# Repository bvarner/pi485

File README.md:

# Pi485 - UART TTL (Raspberry Pi / Arduino) to RS485
## What is it?
Pi485 lets you connect the RX / TX pins on your Raspberry Pi (/dev/ttyAMA0) or Arduino device to an RS-485 network, 
and transmit / receive as if the network were a normal serial device.

## What can it do?
* Create a low-cost RS-485 network of devices using serial I/O.
* Communicate with other RS-485 networks.

Recent models of HVAC equipment (so called, "communicating" units) typically use RS-485 for the physical connection.
This makes deciphering the comms stream a software problem, and one that many people have already started working on!

## Features
All of the project variations in this repository feature the following:

* Termination Jumper. None of the commercial offerings or existing modules I've seen allow you to disable the termination resistor. On a 
multi-module RS-485 network, it's necessary that middle-nodes not have the termination resistor in the circuit, or the bus signals will 
deteriorate significantly.
* Hardware Latched DE / RE pins on the MAX485 driven by TX activity, with a 'RO' (Read Only) jumper header.
Adding a jumper will force your device to be 'read only' by disabling the hardware latch of the DE / RE Pins.
* Software controlable off / on. Using a GPIO pin (3.3v) you can turn the circuit 'on' or 'off', allowing for a software reset of the 485 
module, pseudo "power management", or simply give you the time to setup your UART tty before initiating a communication connection.
If you prefer the 'always on' approach, you can simply hook up positive voltage to the control pin, and the circuit will always be on.

## What's in this repository?
This repository contains [KiCad EDA](http://kicad.org/) source schematics, PCB layouts, and rendered SVG plots.

The SVG Plots can be used to print your own PCB, or you could try using them as a template for making your own.

## What? Make my own PCB?
I've had good success with the layouts in this repo using the laser-printer hot-iron transfer method. I've gotten excellent results with 
Hammermill Color Laser Gloss (sku 163110) paper. It's a 32lb very smooth gloss paper like you'll find on lightweight magazine covers.
The 163110 takes and transfers toner very well, and is light enough for use in nearly every laser printer I've run across.
When soaked in water for a few minutes after ironing the paper easily peels off without removing the toner. I normally lightly sand the 
left-over transfer with 1500 grit paper to remove the last of the paper fibers and any gloss 'bleed' before chemical etching the board.

Now that I have my method down I could probably tweak the layouts to shrink the trace size (from 1.0 to 0.8 or 0.7) which would help with
some of the 'bleed' I sometimes get when doing the iron transfer.

I also have invested in some inexpensive carbide drill bit sets from 0.3 - 1.2mm for drilling the PCBs in a drill press.

If you're interested in a prebuilt board, contact me (bvarner) via github. I would be willing to coordinate a small run, and I may have a 
few boards on hand (or on ebay) you could convince me to part with.

## Usage
To setup a RaspberryPi so that you can use the UART for what you want rather than it exposing a serial console.

1. Use `raspi-config` to disable the serial console.
2. Enable the UART at boot by editing `/boot/config.txt` and setting `enable_uart=1`.
3. A pi485 requires a logic 'high' signal on the PWR (P1 connector, pin 5) signal line. You can wire up a +3.3v line to force power to always
be 'on', or you can control it with a GPIO pin.

If using a GPIO pin, a convenient way to manage this is to install `wiringpi`, and edit the `/etc/rc.local` script to add the following lines:
```
/usr/bin/gpio mode 1 out
/usr/bin/gpio write 1 1
```

You can also take the opportunity to set your tty settings in `/etc/rc.local` if you so desire.

## Hardware Configurations

### Standalone
This complete solution can be assembled from discrete components. It uses a Max485 IC, and NE555 timer, and some discrete components to 
implement a hardware level RS-485 interface that automatically controls the DE / RE pins based on TX activity, allows for jumper 
configuration of termination, and adds blinken-lights for TX / RX, and Power.

This configuration is the easiest one to fabricate at home. Everything from pad size, to trace width and clearance restrictions have been
tweaked to make this easier to work with for novices. Armed with a single-sided copper clad board, some ferric chloride, a fine-tipped 
sharpie marker and a steady hand, you could build this layout without doing an iron transfer. However, the component cost is higher. The
PDIP Max485 in small quantities is by itself more expensive than a single LC Technologies RS485 module used by the bearer configuration.

### Bearer
The bearer board is designed to hold an [LC Tech MAX485 module](http://www.chinalctech.com/index.php?_m=mod_product&_a=view&p_id=811), which
is an inexpensive module based around a max485 in a surface-mount, slew-rate limited configuration. 
These modules include some support components like power filtering capacitors, a power LED, and some pull-up resistors.
Building a bearer board is a bit more tricky, as it has lower clearance tolerances between traces, thinner traces, and requires that you 
modify (unsolder) some resistors off the LC Tech module. However, when full BOM part costs are taken into consideration, if you're making
more than one pi485, it'll be cheaper to use the bearer configuration.

The bearer board adds the 555 latch circuit for DE/RE control from the TX line, RX / TX LEDS, power on/off, and 
jumper termination control from the standalone board design (if you unsolder the 120Ohm resistor on the LC Tech module).

In my experience, if you want to make more than one of these devices, it's much cheaper to purchase the LC Tech modules and build Pi485 
bearer boards to hold them.

## Project Background
I've had a couple Raspberry Pi's laying about my home for a few years now. After running across the 
[Infinitude project](https://github.com/nebulous/infinitude), I realized that my 
HVAC system (a Bryant unit) is actually a 'communicating' system as well. I've had in the back of my mind for some time a project to hook up
a raspberry pi, and track long-term time-series data on my HVAC unit, performance, and temperature differentials.

### Off The Shelf Module Shortcomings / Circuit Analysis / Reasons this project exists.

Almost every module I've looked at is based on the [MAX485](http://datasheets.maximintegrated.com/en/ds/MAX1487-MAX491.pdf).

#### Overly simplistic opinionated view of RS-485.
It seems that off-the-shelf modules tend to approach the MAX485 series of half-duplex (two wire RS485) chips as a pretty simple TTL->485 
converter, suitable for locating at the _endpoints_ of a very simplistic single master-slave network. In order to drop in multiple modules 
(multiple slaves) or enable multi-master communications and form a true network, there's some hardware work that needs to be done (removing
termination resistors) and software control of the RE / DE with a GPIO (which open you up to a whole slew of software timing issues).

#### Soldered on Termination
For example, the LinkSprite module and the LC Tech modules both carry 120Ohm termination resistors, and no jumper header to remove it from
the circuit. The only practical option to add these modules as a network node other than an 'end point' is to unsolder that resistor.

#### Lack of TX / RX Visibility
I like [blinkenlights](https://en.wikipedia.org/wiki/Blinkenlights). These products should have blinkenlights.

#### DE / RE Pin Hysteresis 
Additionally, the LC Tech module has the DE and RE pins of the Max485 directly accessible over headers but provides no extra circuitry to 
drive the input to those pins based off the TTL TX. These two pins of a Max485 are responsible for setting the duplex state of the chip 
(Driver Enable / Receiver Enable) for either sending or receiving data. The RE pin is active on Logic Low (GND) and the DE pin is active on 
Logic High (~20ma of forward voltage). For this reason, you'll commonly see these pins wired together. When set High, the Max485 disables
receiving, and enables transmitting. When pulled low, it enables receiving and disables transmitting. The LC Tech module seems to defy all 
logic and reason in how it wires up the DI, DE, RE, and RO pins. Each pin has a 10k pull-up resistor. So unless you're actively draining 
these pins to ground with your logic circuits,  your max485 is going to end up in "write" mode by _default_. In a multi-master half-duplex
system like an HVAC unit (the initial target application for pi485) this causes a big problem.

I've found many schematics which suggest tying the DE / RE pins to a separate GPIO. This is a terrible idea in practice. In a busy RS485 bus
the time between the DI/DE pins shifting and the start of output on the TX pin would effectively guarantee a collision on the network.

I've also found schematics for RS-232 -> RS-485 converters which work by converting the 232 signal to TTL, then the TTL to RS-485. In these
circuits, they tend to leverage a 555 timer as a time-delayed latch, to hold the DE / RE pins in transmit mode based on the state of the TTL
TX pin. This seems like a really good idea in theory, and in circuit simulations (I don't have a physical scope) it appears that the 555
output will respond quickly enough for at least a 38400baud network to cleanly communicate all the necessary symbols over the wire (given 
the sizing of resistors and capacitors in use with the 555).

In this [555 TTL Latch Simulation](http://tinyurl.com/hx6gfwh), there's a +5V supply, GND, and a H/L logic input (clickable) on the left. 
The output pin of the 555 has a H/L output detector on it, and drives an NPN transistor to turn on an LED. In a real circuit using this 
technique, the 555 output pin would drive the DE/RE pins on a Max485. As an example, checkout the 
[AVT530](http://serwis.avt.pl/manuals/AVT530.pdf), an RS232 to RS485 converter that uses TTL as an intermediary. The schematic is on page 2.

The same company also uses this same 555 & Max485 circuit on their [USB to RS485](http://serwis.avt.pl/manuals/AVT530USB.pdf) converter.

The down-side with these circuits, is that there is a timing differential after the TX pin stops transmitting that the RE pin is held high.
Recall earlier I mentioned things about start / stop bits? This is where that comes into play.
At 38400Hz (as in the simulation above) this delay accounts for an entire clock cycle of bit transmission on the bus. In the interactive 
simulations above, note how if you switch the TTL input high (0 or idle) it takes 2 clocks before the 555 sets the output back low. If your
bit protocol doesn't include a stop bit (idle / high) then the DE / RE will not be disabled at the appropriate time. Without stop bits, you 
will transmit one extra idle (logical 1) on the 485 bus and miss receiving a bit for a clock with these latched circuits.

Here's another [simulation of the 555 latch circuit with pulsed input](http://tinyurl.com/hn6zreu). In this revision, we've added a pull-up
resistor (5k) to the input trigger to hold it 'high' when idle, moved the input clk to drive a decade counter, and tied output pins from the
counter to switch an NPN transistor that sinks the trigger pin low when the counter has a high output. Think of the counter as sending 
logical 1's and 0's by pushing a switch. When the switch (transistor) is closed, the TR voltage drops to ground. If you have start or stop
bits enabled in your stream, this initial drop (0) will be the start bit, which will trigger the 555 output high. In the AVT circuits, this 
drives the RE / DE pins high, putting the MAX485 into transmit mode. An idle 'high' stop bit (Q8) will let the timer's capacitor drain, 
resetting it's output pin. But if you're not using start / stop bits... and you're just getting a stream of bits that is synchronized 
in software, then using a 555 latch is going to be asking for trouble.

In looking at the LinkSprite module, I found it interesting that it dispenses with a time-delay latch and supplies power to the DE / RE pins
via MOSFETS switching a 0.33mA current based upon the TX input. This seems rather 'icky' to me, since logically I would think the DE / RE
pins going 'high' whenever the TTL signal goes idle, would cause an issue. So I threw together a 
[simulation of the TTL input with MOSFET](http://tinyurl.com/glnvxa2) triggers. This confirmed what I thought as far as behavior without 
delay. The good news here, is if you're sending a '0' on the RS-485 bus, you'll transmit that 0, and be prepared to receive any values from
the bus immediately afterward. So if your protocol doesn't use stop bits, you'll be able to read the stream without error. The natural
question at this point is, "what if I'm trying to transmit a '1' (logical TTL high / idle value)?" In that case, the DE pin would be pulled
low, along with the RE pin, putting the MAX485 into Driver disable, Receiver Enabled mode. I'm not sure if this would effectively pulse the
RS-485 bus in an appropriate manner. The Bus signals bits based on bias differences between the two wires, A and B. Something about this
arrangement smells funny.

According to the stuff I've read on RS-485, a driver 'idle' would be A+, B- potentials. After pouring over the Max485 datasheet, I don't see
anything that will lead me to believe RE high / DE low would result in A+, B- potentials being emitted on output lines of the chip.

Nevertheless, it must work... right? Unless the LinkSprite and LC Tech components aren't being tested in multi-master half-duplex 
networks. I have a feeling that's exactly what's going on, since they both carry soldered-on termination resistors that cannot be 
jumper-disabled. That means that if you introduced a network of these devices with more than two nodes, you'd have pretty significant signal
degradation.

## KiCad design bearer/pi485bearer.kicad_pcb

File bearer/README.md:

# Pi485 Bearer Module

Based upon what I learned while creating the Standalone pi485, this board is meant to function as a carrier / bearer for an
[LC Technologies RS485 module](http://www.chinalctech.com/index.php?_m=mod_product&_a=view&p_id=811), adding the RX / TX LEDs,
power controll, and latched DE / RE pin driving to this very inexpensive and commonly available module.

Unlike the standalone board this layout prioritizes compactness over ease of use for beginners.
The trace clearances are tighter and you'll need to remove five surface mount resistors from the RS485 module. In practice, I've found 
these boards are reasonably easy to produce with a laser printer hot iron transfer.

## PCB Layout

is designed to hold these RS485 modules

## Schematic

# Design Goals
* Add the functions and features of the standalone module in a slightly more compact layout that can accomodate inexpensive 485 modules.
* Leverage the RS 485 module due to the module cost being less than the the cost of a discrete terminal block header, max485 IC, power LED, 
LED resistor, and filtering capacitors. These boards do shave a couple USD off the cost of UART based RS-485.
* Latch the DE / RE pins on the Max485 based upon the UART TX activity, but allow that to be disabled (force read-only mode)
* Include jumper termination for the A/B lines of the RS485 bus.

For in-depth details on the function of [the circuit](plots/pi485bearer.png) refer to the [Standalone Module README](../standalone/README.md).

# Build Instructions

1. Start off by customizing the resistor values for your LEDs. I used [http://ledcalc.com/] to help inspire my choices.
2. Use KiCad's PCB editor (pcbnew) to customize any footprint changes.
3. Print the [back copper](plots/pi485bearer-B.Cu.svg) layer on a laser printer, using glossy photo paper.
4. Print the [front](plots/pi485bearer-brd.svg) layers on a laser printer, using glossy photo paper.
5. Cut your board (62mm x 30mm)
6. Transfer the copper printout using a hot iron and some water.... (youtube reference coming). Touchup with a resist pen if necessary.
7. Etch the board.
8. Clean the board.
9. Tin the board.
10. Reflow the board (bake it in an oven).
11. Drill the component holes.
12. Place & solder components.
13. Assemble!
14. Remove the 120Ohm resistor (R7), and the 4 10kOhm pull-up resistors (R1 - R4) from the LC Tech 485 Module.

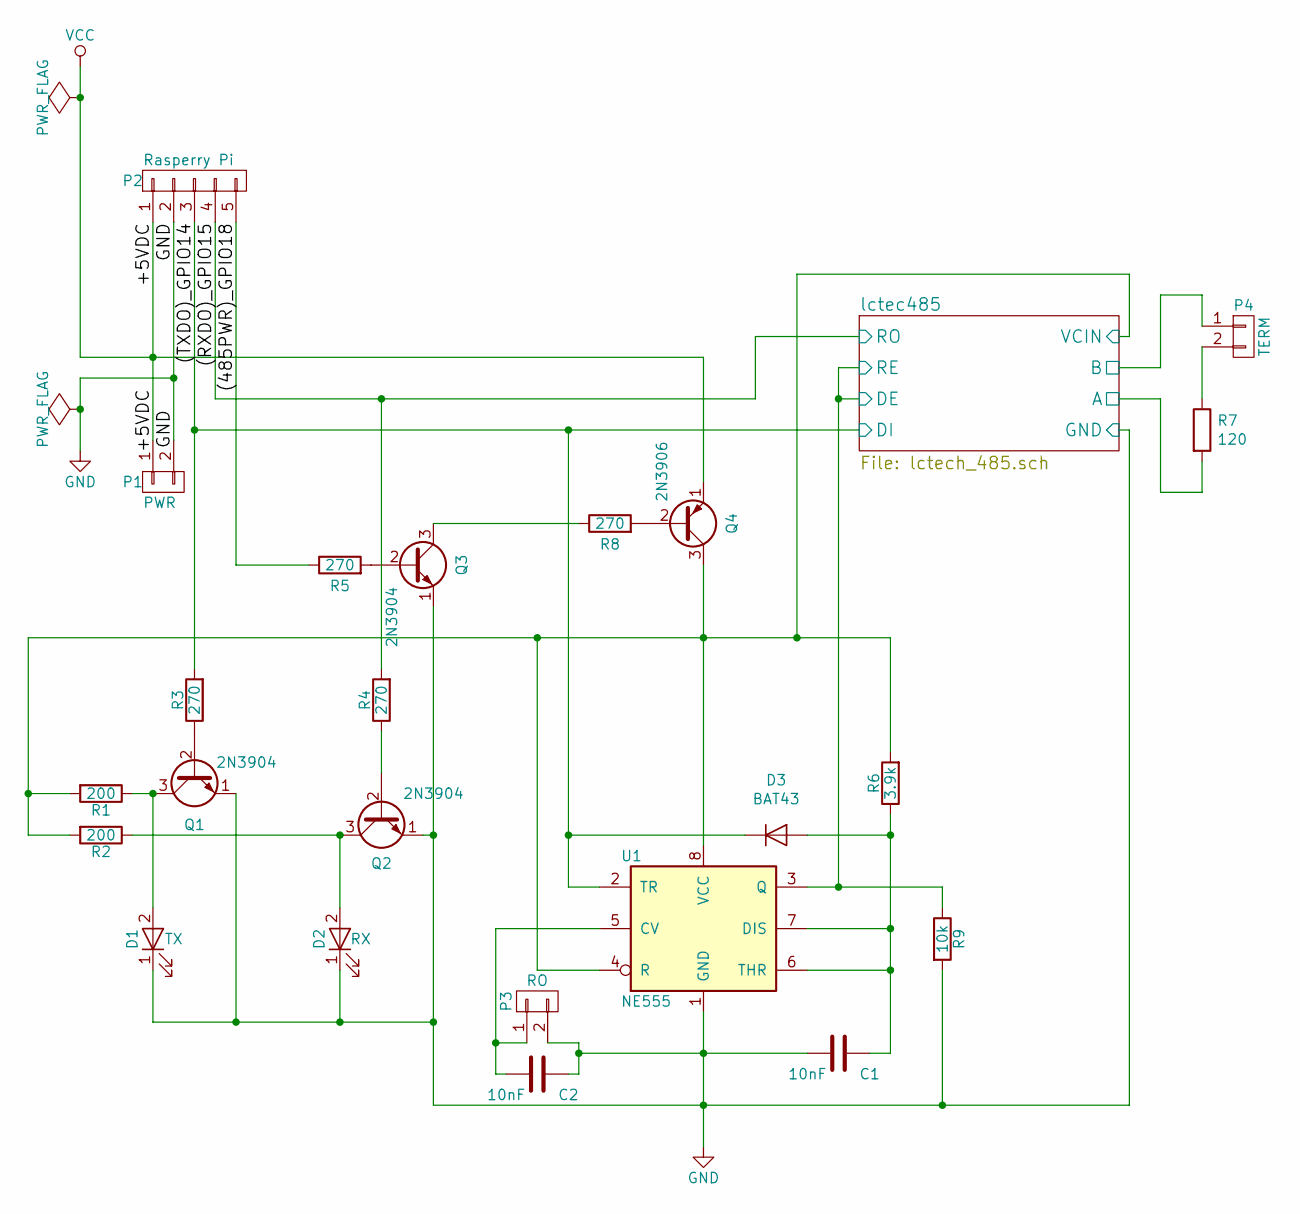
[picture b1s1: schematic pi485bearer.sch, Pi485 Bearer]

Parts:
C1, C2: 10nF; C_Rect_L4_W2.5_P2.5
D1: TX; LED-3MM
D2: RX; LED-3MM
D3: BAT43; Diode_DO-35_SOD27_Horizontal_RM10
P1: PWR; Pin_Header_Straight_1x02
P2: Rasperry Pi; Pin_Header_Straight_1x05
P3: RO; Pin_Header_Straight_1x02
P4: TERM; Pin_Header_Straight_1x02
Q1, Q2, Q3: 2N3904; TO-92_Inline_Wide
Q4: 2N3906; TO-92_Inline_Wide
R1, R2: 200; Resistor_Horizontal_RM7mm
R3: 270; Resistor_Horizontal_RM10mm
R4, R5, R8: 270; Resistor_Horizontal_RM7mm
R6: 3.9k; Resistor_Horizontal_RM10mm
R7: 120; Resistor_Horizontal_RM10mm
R9: 10k; Resistor_Horizontal_RM15mm
U1: NE555; DIP-8_W7.62mm_LongPads

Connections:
/(485PWR)_GPIO18: P2.5, R5.1
/(RXDO)_GPIO15: P2.4, R4.2; also elsewhere on the board
/(TXDO)_GPIO14: D3.1 (K), P2.3, R3.2, U1.2 (TR); also elsewhere on the board
/lctec485/A: R7.2; also elsewhere on the board
/lctec485/B: P4.1; also elsewhere on the board
/lctec485/DE: R9.1, U1.3 (Q); also elsewhere on the board
/lctec485/VCIN: Q4.3 (C), R1.2, R2.2, R6.2, U1.4 (R), U1.8 (VCC); also elsewhere on the board
GND: C1.2, C2.1, D1.1 (K), D2.1 (K), P1.2, P2.2, P3.2, Q1.1 (E), Q2.1 (E), Q3.1 (E), R9.2, U1.1 (GND); also elsewhere on the board
unnamed: C1.1, D3.2 (A), R6.1, U1.6 (THR), U1.7 (DIS)
unnamed: C2.2, P3.1, U1.5 (CV)
unnamed: D1.2 (A), Q1.3 (C), R1.1
unnamed: D2.2 (A), Q2.3 (C), R2.1
unnamed: P4.2, R7.1
unnamed: Q1.2 (B), R3.1
unnamed: Q2.2 (B), R4.1
unnamed: Q3.2 (B), R5.2
unnamed: Q3.3 (C), R8.1
unnamed: Q4.2 (B), R8.2
VCC: P1.1, P2.1, Q4.1 (E)

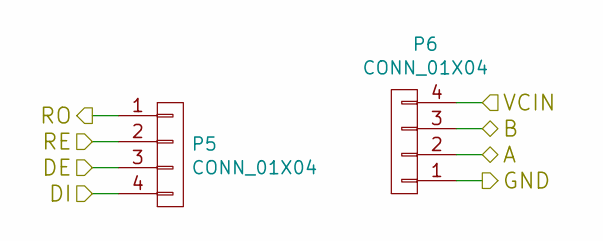
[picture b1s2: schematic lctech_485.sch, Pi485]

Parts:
P5, P6: CONN_01X04; Socket_Strip_Straight_1x04

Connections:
/(RXDO)_GPIO15: P5.1; also elsewhere on the board
/(TXDO)_GPIO14: P5.4; also elsewhere on the board
/lctec485/A: P6.2; also elsewhere on the board
/lctec485/B: P6.3; also elsewhere on the board
/lctec485/DE: P5.2, P5.3; also elsewhere on the board
/lctec485/VCIN: P6.4; also elsewhere on the board
GND: P6.1; also elsewhere on the board

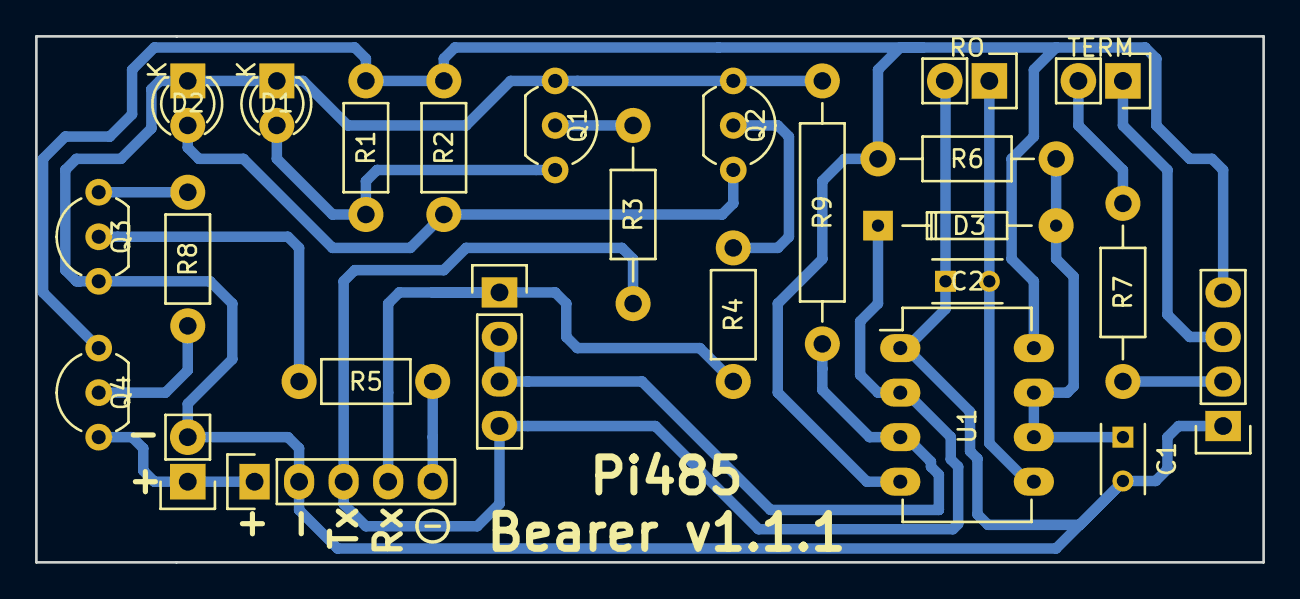
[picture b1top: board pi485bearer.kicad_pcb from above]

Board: 2 copper layers, 70.0 x 30.0 mm, 25 parts (0 on the bottom side), 19 nets.

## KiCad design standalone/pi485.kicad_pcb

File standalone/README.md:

# Pi485 Standalone Module

This is a stand-alone module for RS-485 communication, utilizing a MAX485 IC and a NE555 Timer IC.
The PCB for this project is the most 'simple' of the two to etch yourself. Most of the pads are 
oversized, the copper traces are significantly wider and spaced far enough that it's possible 
to create a PCB with a resist marker by hand. 

## PCB Layout

## Assembled

## Schematic

# Design Goals
* [Simple / Easy To Understand Circuit](plots/pi485.png)
* Easily fabricated at home with simple tooling
* Reasonably inexpensive to source parts for and build (~$20 or less)
* Latch the DE / RE pins on the Max485 based upon the UART TX activity, but allow that to be disabled (force read-only mode)
* Include jumper termination for the A/B lines of the RS485 bus.

To achieve these goals the PCB layout in this repository is a single-side clad board, components on the front, copper on the back.
The traces are large (0.4mm!), the pads are oversized where possible, and I've allowed plenty of clearance between traces and pads, making
it possible to touch-up a hot-iron transfer with an ink-resist pen. You may even be able to draw the existing tracks with a pen free-hand.

For tooling, you'll need the 'standard' PCB etching supplies; a bottle of Ferric Chloride, some isopropyl alcohol, gloves, 
a dish to do the etching, and an appropriately sized drill bit. (I had a 0.040" bit in a set) I'd recommend you have a drill press, too.

I highly recommend doing a hot-iron transfer of laser printer toner. Print the SVGs using a laser printer onto glossy photo (or magazine)
paper. Heat the board with an iron, then stick the printout to the board. Press the printout firmly to the board using the hot iron (you're
goal is to melt the toner to the board surface), and then start soaking with water and continue steaming. Firm pressure and heat will do a
good job of sticking the printout onto the board. It works surprisingly well. Once you've steamed the paper (or soaked it in water) and it
starts to fall of the board, you can touchup any trace or pad issues with a resist pen, and etch the board.

I also use a kitchen oven to bake the board once it's tinned. Getting it up to ~425 degrees F does a nice job of reflowing the solder,
which makes it much easier to drill the holes.

# Circuit Analysis / Explanation

## TTL Serial Communication Basics
TTL signaling of serial data idles 'high'. When data is being transmitted on the TX pin, it first drops 'low' (a start bit), 
transmits it's data, and then sends a stop bit. In TTL, a logical 0 is GND. A Logical 1 is +V. But when there are no transmissions taking 
place, the pin holds 'high', at +V. I personally found [this SparkFun tutorial](https://www.sparkfun.com/tutorials/215) to be highly 
educational on the nuances of TTL. If your protocol doesn't include a start / stop bit, this can be problematic for converting TTL 
_transmissions_ to RS-485.

## Schematic Breakdown
The [current schematic](plots/pi485.png) is fairly straightforward.

All of the resistor values connected directly to LEDs should be double-checked for your LED selections.

## Power Input / Signal Connections
Starting in the upper left quadrant of the schematic, you have the input header pins (P1). There's a second pair of headers for an additional
+5vdc and ground connections (P2). I use the second two-pin header to connect my power supply, then connect the other pins to the Pi providing
power to the RaspberryPi and connecting the UART pins and 485PWR signal line.

## RX / TX LED Signaling
The RX & TX lines are tapped with 270ohm resistors to pull the 5vdc down to an appropriate level for tripping the NPN transistors in the 
lower left side of the schematic. When the voltage on the RX / TX pins goes LOW (signaling data, not idle), the NPN halts the flow of 
electricity from the Collector to the Emitter (opens the switch), leaving the only path to ground being through the LEDs. Make sure you 
size your R3 and R7 resistors appropriately for your LEDs. The NPN transistors in this circuit are specced as 2N3904's, but 2N4401s will 
work just as well.

## Power Filtering & Power LED 
Above the RX / TX LED section, there's a small block with two transistors (an NPN and a PNP) working together to create a 'high-side' power
switch for the entire circuit. The PNP transistor switches the +5v supply for the rest of the circuit, based on the on/off state of the 
NPN. Using the NPN to control the PNP allows us to drive the 5v line with a 3.3v GPIO, and to do it in a '1' is on, '0' is off, semantic.

If you'd rather the circuit always be 'on', omit these components, or connect pin 5 on the P1 header to the 5V or a 3.3V line.

Looking to the lower-right portion of the schematic, you'll find several decoupling filter capacitors and a power LED.

## UART TX Connections
The TX line is connected to the trigger pin of a 555 timer, and then to the Data Input pin of the Max485.

The 555 timer circuit is a slightly modified missing pulse detector, which you'll find right smack in the middle of the schematic.

When the TX power drops below the threshold defined by the 3.9k resistor (R2), the output of the 555 goes HIGH. After a very short delay,
(it switches ~38400hz) the output will go back low, unless the the TX line input is still low. In a typical missing pulse detector, the 555
output will go back low regardless of the TX line (555 trigger) input. The addition of the shottky diode changes this configuration, and 
holds the output steady so long as the input is steady. The diode has to be capable of switching reverse voltage bias fast enough to keep
the input lower than the threshold / discharge output, but without affecting the input signal line. Hence the use of the BAT43, rather than
a 'normal' silicon diode.

The output of the 555 timer is used to set the input on the DE / RE (Driver Enable / Receiver Enable) pins on the max485. When HIGH, the 
Driver Enable is set, putting the Max485 into 'master' mode and broadcasting on the 485 bus. When LOW, the RE pin (which has inverted logic
on a Max485) is enabled, putting the Max485 into 'receive' mode.

If there is a jumper present on the CTRL pin (5) of the 555 timer, the 555 output will always be 'LOW' effectively holding the Max485 in 
Receive mode forever.

## UART RX Connection
Moving along the RX line, it's connected to the Data Output pin of the Max485.

## Max485 Output
The output pins of the Max485 are configured to setup a high-resistance reference against the current 'ground', and to allow the termination
(120 Ohm) resistor to be removed from the circuit.

## Putting it all together...
The circuit provides basic decoupling / power filtering, some passive LED monitoring of RX / TX lines, and a latch-based DE / RE driver 
logic for the Max485, along with a basic resistance network to setup the A/B differentials on the RS-485 bus.

# Analysis of other products / options
I am not a professional EE. In reality I'm a software engineer who got into this out of curiosity. I have always detested 
black-boxes (things which I cannot take apart or understand completely) and it's my nature to dismantle, analyze, evaluate, and eventually 
take that knowlege and apply it to things I synthesize. I consider electronics a 'hobby'. My comments here are my own personal opinions
and are not an endorsement or meant to dissuade or persuade your purchasing decisions.

# Build Instructions

1. Start off by customizing the resistor values for your LEDs. I used [http://ledcalc.com/] to help inspire my choices.
2. Use KiCad's PCB editor (pcbnew) to customize any footprint changes.
3. Print the [back copper](plots/pi485-B.Cu.svg) layer on a laser printer, using glossy paper.
4. Print the [front](plots/pi485-brd.svg) layers on a laser printer, using glossy paper.
5. Cut your board to size (63mm x 46mm)
6. Transfer the copper printout using a hot iron and some water.... (youtube reference coming). Touchup with a resist pen if necessary.
7. Etch the board.
8. Clean the board.
9. Tin the board.
10. Reflow the board (bake it in an oven).
11. Drill the component holes.
12. Place & solder components.
13. Clean up, and enjoy!

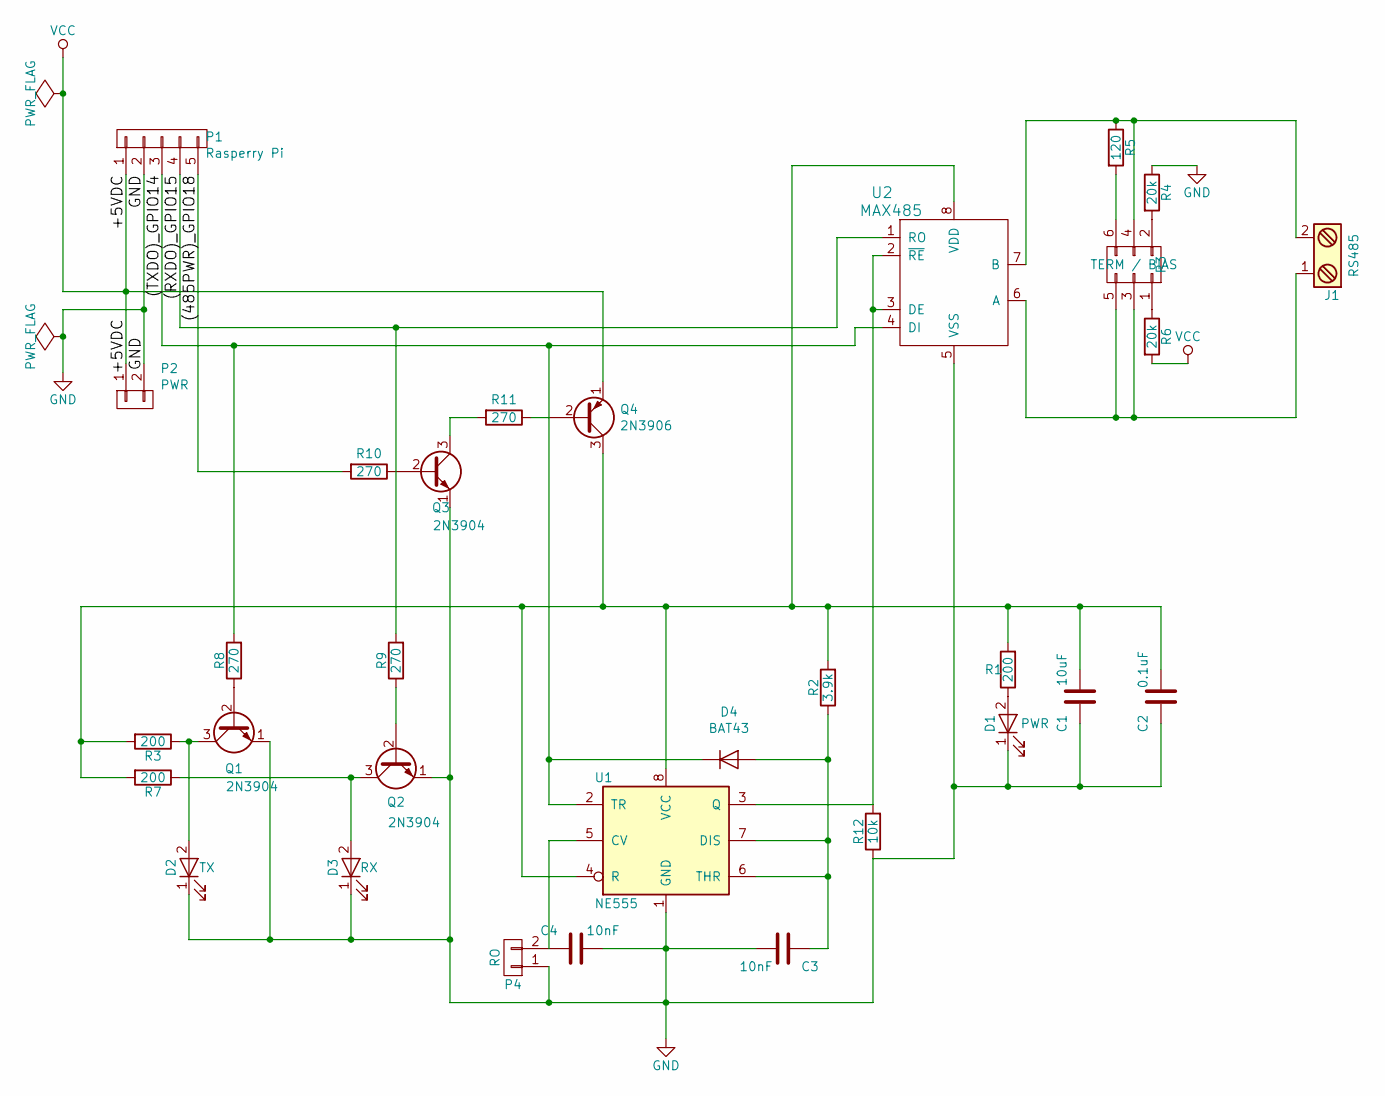
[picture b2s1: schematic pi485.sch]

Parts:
C1: 10uF; C_Radial_D5_L11_P2
C2: 0.1uF; C_Rect_L7_W2.5_P5
C3: 10nF; C_Rect_L7_W2.5_P5
C4: 10nF; C_Rect_L4_W2.5_P2.5
D1: PWR; LED-3MM
D2: TX; LED-3MM
D3: RX; LED-3MM
D4: BAT43; Diode_DO-35_SOD27_Horizontal_RM10
J1: RS485; TerminalBlock_Pheonix_MPT-2.54mm_2pol
P1: Rasperry Pi; Pin_Header_Straight_1x05
P2: PWR; Pin_Header_Straight_1x02
P3: TERM / BIAS; Pin_Header_Straight_2x03
P4: RO; Pin_Header_Straight_1x02
Q1, Q2, Q3: 2N3904; TO-92_Inline_Wide
Q4: 2N3906; TO-92_Inline_Wide
R1: 200; Resistor_Horizontal_RM7mm
R2: 3.9k; Resistor_Horizontal_RM10mm
R3, R7: 200; Resistor_Horizontal_RM10mm
R4, R6: 20k; Resistor_Horizontal_RM7mm
R5: 120; Resistor_Horizontal_RM10mm
R8, R9, R10, R11: 270; Resistor_Horizontal_RM10mm
R12: 10k; Resistor_Horizontal_RM7mm
U1: NE555; DIP-8_W7.62mm_LongPads
U2: MAX485; DIP-8_W7.62mm_LongPads

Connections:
/(485PWR)_GPIO18: P1.5, R10.2
/(RXDO)_GPIO15: P1.4, R9.2, U2.1 (RO)
/(TXDO)_GPIO14: D4.1 (K), P1.3, R8.2, U1.2 (TR), U2.4 (DI)
GND: C1.1, C2.1, C3.2, C4.2, D1.1 (K), D2.1 (K), D3.1 (K), P1.2, P2.2, P4.1, Q1.1 (E), Q2.1 (E), Q3.1 (E), R4.1, R12.1, U1.1 (GND), U2.5 (VSS)
unnamed: C1.2, C2.2, Q4.3 (C), R1.2, R2.2, R3.2, R7.2, U1.4 (R), U1.8 (VCC), U2.8 (VDD)
unnamed: C3.1, D4.2 (A), R2.1, U1.6 (THR), U1.7 (DIS)
unnamed: C4.1, P4.2, U1.5 (CV)
unnamed: D1.2 (A), R1.1
unnamed: D2.2 (A), Q1.3 (C), R3.1
unnamed: D3.2 (A), Q2.3 (C), R7.1
unnamed: J1.1, P3.3, P3.5, U2.6 (A)
unnamed: J1.2, P3.4, R5.1, U2.7 (B)
unnamed: P3.1, R6.1
unnamed: P3.2, R4.2
unnamed: P3.6, R5.2
unnamed: Q1.2 (B), R8.1
unnamed: Q2.2 (B), R9.1
unnamed: Q3.2 (B), R10.1
unnamed: Q3.3 (C), R11.2
unnamed: Q4.2 (B), R11.1
unnamed: R12.2, U1.3 (Q), U2.2 (~RE), U2.3 (DE)
VCC: P1.1, P2.1, Q4.1 (E), R6.2

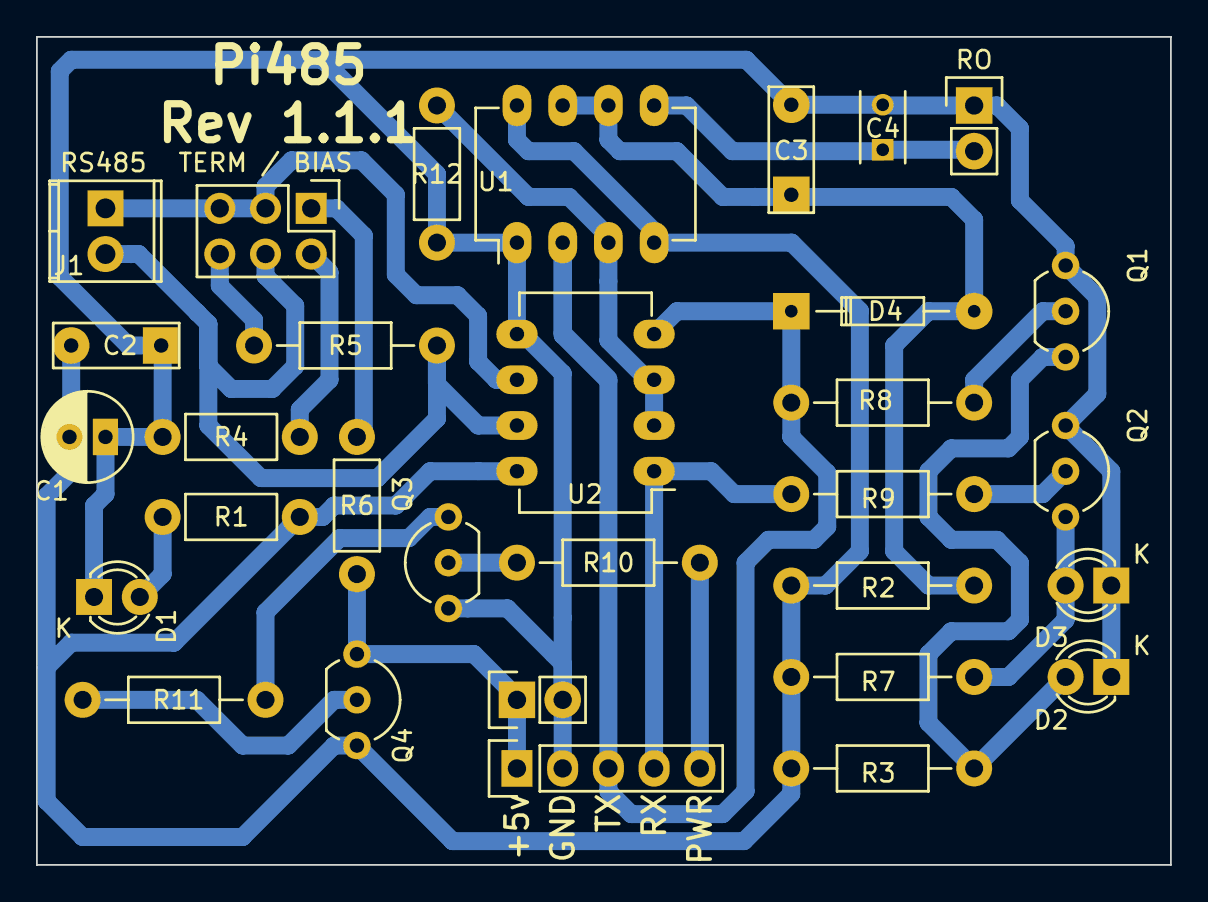
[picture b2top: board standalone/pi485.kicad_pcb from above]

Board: 2 copper layers, 63.0 x 46.0 mm, 31 parts (0 on the bottom side), 22 nets.

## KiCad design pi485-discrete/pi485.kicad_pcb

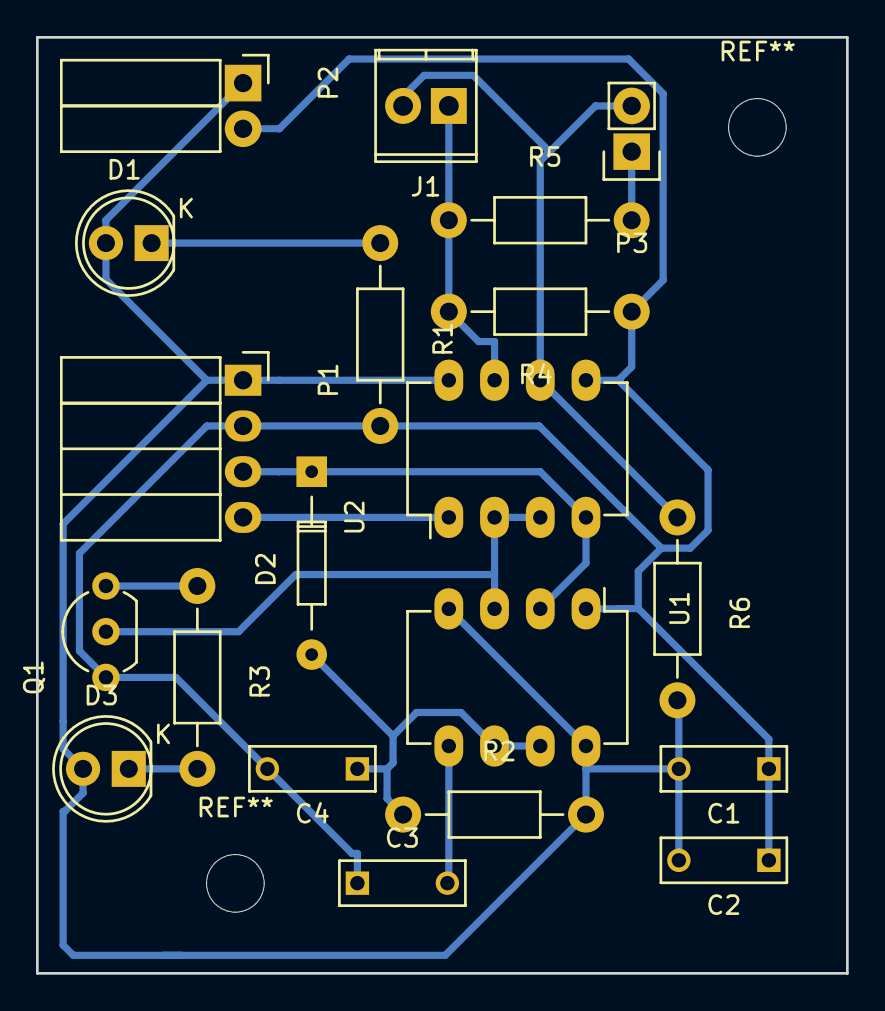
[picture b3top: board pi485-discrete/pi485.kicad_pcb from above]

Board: 2 copper layers, 45.0 x 52.0 mm, 20 parts (0 on the bottom side), 13 nets.

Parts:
C1: 0.1uF; C_Rect_L7_W2.5_P5
C2: 10uF; C_Rect_L7_W2.5_P5
C3, C4: 10nF; C_Rect_L7_W2.5_P5
D1: PWR; LED-5MM
D2: BAT43; Diode_DO-35_SOD27_Horizontal_RM10
D3: TX; LED-5MM
J1: RS485; TerminalBlock_Pheonix_MPT-2.54mm_2pol
P1: Rasperry Pi; Socket_Strip_Angled_1x04
P2: PWR; Socket_Strip_Angled_1x02
P3: Term; Pin_Header_Straight_1x02
Q1: NPN; TO-92_Inline_Wide
R1: 1k; Resistor_Horizontal_RM10mm
R2: 3.9k; Resistor_Horizontal_RM10mm
R3: 470; Resistor_Horizontal_RM10mm
R4, R6: 20k; Resistor_Horizontal_RM10mm
R5: 120; Resistor_Horizontal_RM10mm
U1: NE555; DIP-8_W7.62mm_LongPads
U2: MAX485; DIP-8_W7.62mm_LongPads

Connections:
/(RXDO)_GPIO15: P1.4, U2.1
/(TXDO)_GPIO14: D2.1, P1.3, U1.2, U2.4
GND: C1.1, C2.1, C3.1, C4.2, P1.2, P2.2, Q1.1, R1.2, R4.1, U1.1, U2.5
unnamed: C3.2, U1.5
unnamed: C4.1, D2.2, R2.1, U1.6, U1.7
unnamed: D1.1, R1.1
unnamed: D3.1, R3.2
unnamed: J1.1, R4.2, R5.1, U2.7
unnamed: J1.2, P3.2, R6.1, U2.6
unnamed: P3.1, R5.2
unnamed: Q1.2, U1.3, U2.2, U2.3
unnamed: Q1.3, R3.1
VCC: C1.2, C2.2, D1.2, D3.2, P1.1, P2.1, R2.2, R6.2, U1.4, U1.8, U2.8

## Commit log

2017-01-09 initial add of discrete version
2017-01-09 Eh, updating the readme.
2017-01-11 Initial checkin of current work. This stuff does not work
2017-01-12 Made a bunch of changes...
    New board size (70mm x 53mm) single layer, better layout.
    Replace silicon diode with saturated NPN, added NPN tirggered TX / RX LEDs.
2017-01-12 Updating...
2017-01-12 Removed dimensions.
2017-01-12 Original plot exports
2017-01-12 Converted to raster in red / blue
2017-01-12 Updated layer selection
2017-01-13 Removed the huge PDFs.
2017-01-13 Switched A/B output on the RS485 screw terminal for pin 1 to be A, pin 2 to be B.
2017-01-13 Forgot to bump the PCB.
2017-01-13 artifacts.
2017-01-13 Resistor / LED adjustments, BAT43 restoration (digi-key order placed). Footprint updates.
2017-01-13 Updated the PCB, tweaked some routes and pad sizes.
2017-01-13 Some tweaks
2017-01-17 * Rotated board 90 degrees. * Major update to footprints. Resistors are 10mm, LEDs are 3mm. * Manually re-routed / cleaned up traces & positiiong of quite a few things. * This could be pulled so much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
2017-01-17 Oh yeah, the date.
2017-01-17 Trying to embed pdfs...
2017-01-17 PNG time.
2017-01-17 Mirrored. Really.
2017-01-17 Trying to link to the PDF from the image
2017-01-17 I think I must be getting tired
2017-01-17 Added SVGs. Replotted the front of the board.
2017-01-18 Fixed the footprint issues with the 2N4401 transistors being 'backwards'
2017-01-18 Board #0!
    I built a board tonight. It worked perfectly.
2017-01-18 Adding some photos of board #0
2017-01-18 1.1.0 bump. Added 3.3v control pin to turn on power to the 485 and the PWR LED.
2017-01-18 VCC control of the 555. Using a GPIO pin, we can reduce overall power consumption by turning things off when we don't need them.
2017-01-19 * Added 3.3v enable / disable pin. Can be tied to 3.3v output on the pi, or a GPIO pin to force power off / on of the pi485 circuits. * Enables software control of a RS485 'reset', and will make it e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
2017-01-19 Hey look, mounting holes.
2017-01-19 Updated the svgs
2017-01-19 Updated svgs again.
2017-01-20 Made a carrier board for lc-tech with the 555 trigger, and gpio-controlled power.
2017-01-24 Carrier updates.
2017-01-30 Renaming carrier to bearer...
2017-02-07 Updating documentation, removing artifacts.
2017-02-07 Cleaning up intermediary files.
2017-02-07 Renamed bearer.
2017-02-07 Updating With rendered SVG plots
2017-02-07 Adding mogrified PNGs
2017-02-07 Include images
2017-02-07 links...
2017-02-07 Readme for Bearer board.
2017-02-07 Bump
2017-02-07 Removing photos of first board
2017-02-07 Fixed link, added schematic.
2017-02-07 testing the svg from github
2017-02-07 testing the svg from github... didn't work
2017-02-07 docs
2017-02-07 Replot using small drill marks.
2017-02-07 Trimmed pngs
2017-02-07 Updated export plots.
2017-02-07 Updated PNGs
2017-02-07 Rendering boards better.
2017-02-07 Updated Plots
2017-02-07 Clarification.
2017-02-07 Include the PCB plots on the main README
2017-02-07 Increased trace thickness
2017-02-07 Updated bearer traces
2017-02-07 Updated bearer with mount holes
2017-02-07 Updated bearer with mount holes... and updated PNGs
2017-02-07 Trace revisions....
2017-02-07 yuuup
2017-02-07 kicad link, some minor wording, now that I've updated the bearer layout.
2017-02-07 yeah, yank that.
2017-02-08 Esthetics on the standalone board.
2017-02-08 Symmetry is beautiful.
2017-02-08 Well that wasn't the file I thought it would be.
2017-02-08 Updates and what-not for asthetics.
2017-02-08 Updates for drill marks and bearer rendering
2017-02-08 Some additional cleanup and re-routing
2017-02-09 Updated with TERM / RO values in schemas and PCBs
2017-02-09 Documentation consistancy
2017-02-09 spacing
2017-02-10 Low-side NPN switching. We'll see if things 'floating' causes issues... if so, I'll have to order a few PNP's to use for high-side switching.
2017-02-12 Updated standalone for asthetics.
2017-02-12 standalone reconfigured for high-side PNP switching
2017-02-12 high-side PNP power switching for the bearer.
2017-02-12 Esthetics and what-not...
2017-02-13 Moved the P1 P2 connectors to make a bit more sense, enlarged the bearer to 70mm, four mount holes per board.
2017-02-14 Removed an unnecessary junction.
2017-02-14 Updates for read-mes, and what-not
2017-02-14 Docs update
2017-02-14 Documentation.
2017-02-16 * Found a huge issue with the bearer... where the TX and RX were backwards, due to the header for the module being ... um... reversed. :-/
2017-02-16 * Re-placed & routed the bearer, now with the headers in the proper orientation. *facepalm*
2017-02-16 Conformity
2017-02-17 Increased trace size, clearance for PCB etching / printability.
2017-02-17 Updated renders.
2017-02-17 Photos.
2017-02-17 Scale... oh my
2017-02-17 Documentation
2017-02-17 Better organization
2017-02-17 more.
2017-02-17 uh oh
2017-02-20 1.1.1 schematics, trace plots, etc.
2017-02-21 This was caused by over-volting the supply, which caused the voltage divider for the 555 to put the 3.0v from the TX idle out of range of resetting the 555. Hah!
2017-02-21 Updates for jumpered biasing on standalone boards. The silly bearer modules you can just unsolder the biasing resistors if it becomes an issue. I should probably add jumpering for that too, but at th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
2017-02-21 Added a script to render svg plots to png.
2017-02-23 Pretty much it for 1.1.1
2017-02-23 Uh, wrong number, dude.
2021-11-09 Update README.md
    https://forum.kicad.info/t/warning-avoid-all-links-to-kicad-pcb-org-use-kicad-org/31521
